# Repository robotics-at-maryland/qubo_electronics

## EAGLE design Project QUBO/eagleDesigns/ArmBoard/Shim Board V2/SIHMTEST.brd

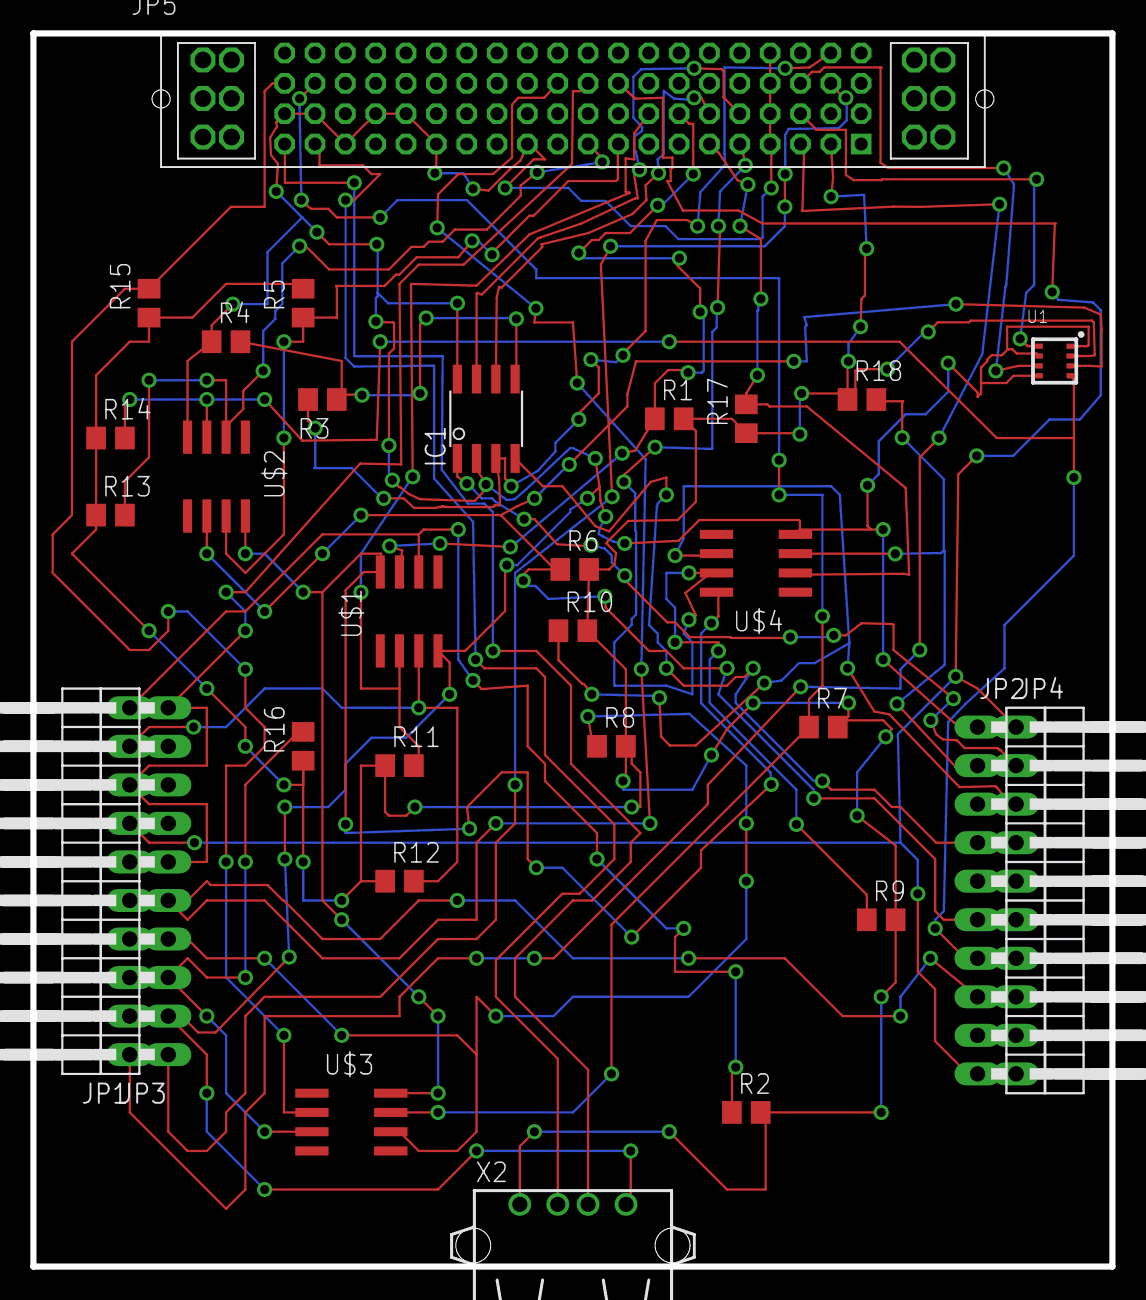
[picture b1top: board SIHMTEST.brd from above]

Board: 2 copper layers, 71.1 x 81.3 mm, 30 parts (0 on the bottom side), 34 nets.

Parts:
IC1: MCP2551/SN; SO08
JP1, JP2, JP3, JP4: 1X10/90
JP5: MPSC-01-80
R1, R2, R5, R6, R7, R8, R9, R10, R11, R12, R13, R14, R15, R16, R17, R18: 5k; R0805
R3, R4: 10k; R0805
U1: BME280; BME280_LGA
U$1, U$2, U$3, U$4: P82B715; SO8
X2: USB

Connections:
3.3(1): JP1.1, JP5.3
3.3(VDDBME): JP5.23, U1.P$8
3.3(VDDIOBME): JP5.43, U1.P$6
5.0(3): JP3.1, JP5.42
5.0(BME): JP5.2, R1.2, R2.2, R5.2, R6.2, R7.2, R8.2, R9.2, R10.2, R11.1, R12.1, R13.1, R14.1, R15.1, R16.1, R17.1, R18.1, U1.P$2, X2.1
BUFFERSCL0: JP5.28, R11.2, U$1.2
BUFFERSCL1: JP5.10, R13.2, U$2.2
BUFFERSCL2: JP5.60, R15.2, U$3.2
BUFFERSCL3: JP5.6, R17.2, U$4.2
BUFFERSDA0: JP5.27, R1.1, U$1.7
BUFFERSDA1: JP5.9, R5.1, U$2.7
BUFFERSDA2: JP5.59, R7.1, U$3.7
BUFFERSDA3: JP5.5, R9.1, U$4.7
BUFFERVCC: U$1.8, U$2.8, U$3.8, U$4.8
CANH: IC1.7, JP5.25
CANL: IC1.6, JP5.26
CANRX: IC1.4, JP2.4
CANTX: IC1.1, JP4.2
GND: IC1.2, IC1.8, JP2.1, JP3.2, JP5.4, JP5.12, JP5.15, JP5.18, JP5.24, JP5.36, JP5.37, JP5.39, JP5.40, JP5.44, JP5.64, R4.1, U1.P$1, U1.P$5, U1.P$7, U$1.4, U$2.4, U$4.4, X2.4
MISO: JP2.8, JP3.5, JP5.51
MOSI: JP1.8, JP3.6, JP3.10, JP5.50
unnamed: IC1.5, R3.1, R4.2
SPI_CLK: JP1.7, JP2.10, JP4.1, JP5.49
UNBUFFERSCL0: JP1.9, R12.2, U$1.3
UNBUFFERSCL1: JP2.7, R14.2, U1.P$4, U$2.3
UNBUFFERSCL2: JP3.3, R16.2, U$3.3
UNBUFFERSCL3: JP2.2, R18.2, U$4.3
UNBUFFERSDA0: JP1.10, R2.1, U$1.6
UNBUFFERSDA1: JP2.6, R6.1, U1.P$3, U$2.6
UNBUFFERSDA2: JP3.4, R8.1, U$3.6
UNBUFFERSDA3: JP4.3, R10.1, U$4.6
USB+: JP5.20, X2.3
USB-: JP5.19, X2.2
VDD: IC1.3, JP5.62, R3.2

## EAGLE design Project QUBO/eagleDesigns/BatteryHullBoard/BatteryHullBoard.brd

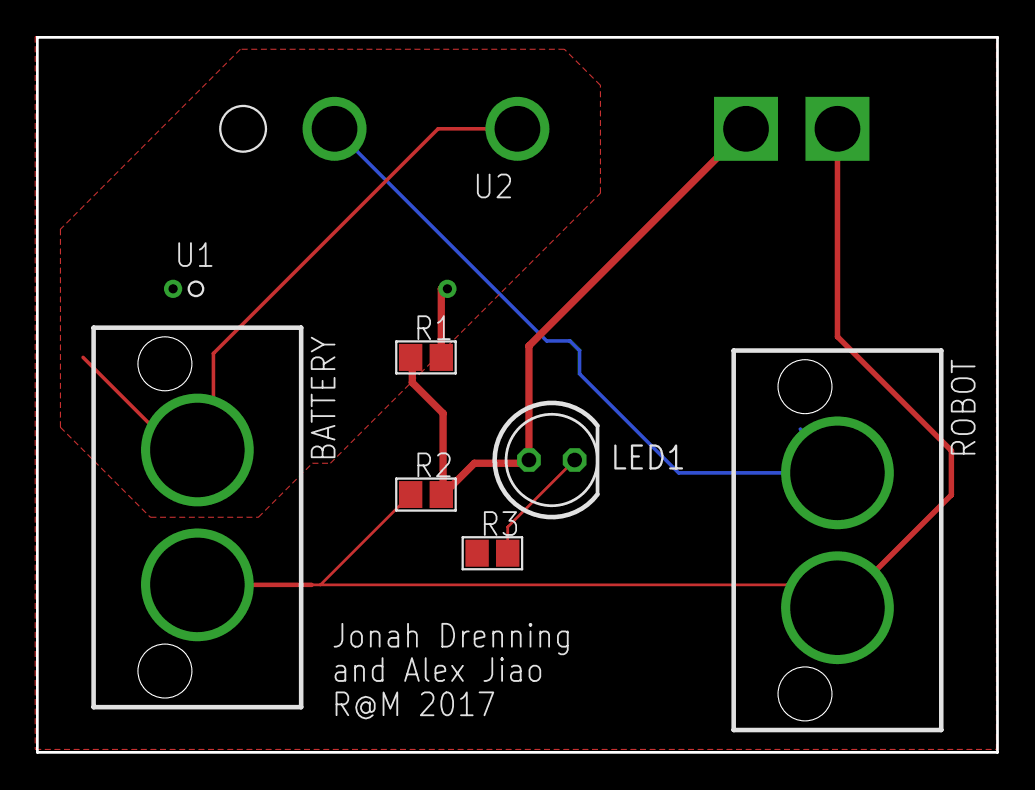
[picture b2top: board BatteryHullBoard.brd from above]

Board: 2 copper layers, 53.3 x 39.7 mm, 8 parts (0 on the bottom side), 6 nets.

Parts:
BATTERY: 2_SUPERSABRE; SUPERSABRE_2CIRCUIT
LED1: LED5MM
R1: 1000; R0805
R2: 7700; R0805
R3: 10000; R0805
ROBOT: 2_SUPERSABRE; SUPERSABRE_2CIRCUIT
U1: KSK-1E66
U2: CMXSIPSSR

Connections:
GND: BATTERY.P$2, R2.1, R3.1, ROBOT.P$2, U2.P$4
unnamed: R1.2, U1.P$2
unnamed: LED1.A, R1.1, R2.2, U2.P$3
unnamed: LED1.K, R3.2
PWR1: BATTERY.P$1, U1.P$1, U2.P$2
PWR2: ROBOT.P$1, U2.P$1

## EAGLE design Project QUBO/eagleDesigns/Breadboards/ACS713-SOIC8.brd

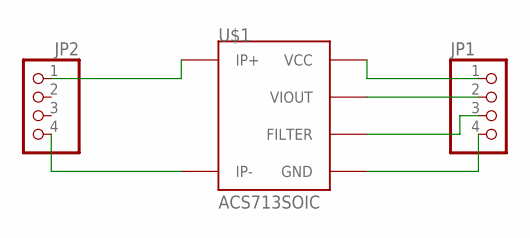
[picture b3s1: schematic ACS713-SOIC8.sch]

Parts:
JP1, JP2: PINHD-1X4; 1X04
U$1: ACS713SOIC; ACS713-SOIC

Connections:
unnamed: JP2.1, U$1.P$1 (IP+), U$1.P$2 (IP+)
unnamed: JP2.4, U$1.P$3 (IP-), U$1.P$4 (IP-)
unnamed: JP1.4, U$1.P$5 (GND)
unnamed: JP1.3, U$1.P$6 (FILTER)
unnamed: JP1.2, U$1.P$7 (VIOUT)
unnamed: JP1.1, U$1.P$8 (VCC)

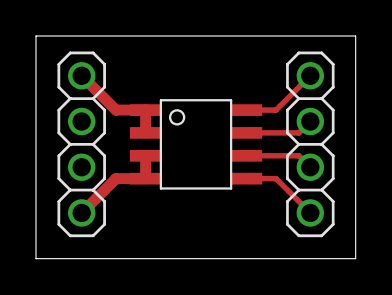
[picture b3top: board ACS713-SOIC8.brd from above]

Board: 2 copper layers, 17.8 x 12.4 mm, 3 parts (0 on the bottom side), 6 nets.

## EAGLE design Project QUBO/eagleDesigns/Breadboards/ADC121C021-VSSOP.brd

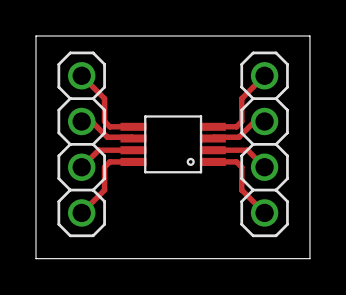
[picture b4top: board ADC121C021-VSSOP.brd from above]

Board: 2 copper layers, 15.2 x 12.4 mm, 3 parts (0 on the bottom side), 8 nets.

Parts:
JP1, JP2: 1X04
U$1: ADC121C021; VSSOP-8

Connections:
unnamed: JP1.1, U$1.P$1
unnamed: JP1.2, U$1.P$2
unnamed: JP1.3, U$1.P$3
unnamed: JP1.4, U$1.P$4
unnamed: JP2.1, U$1.P$5
unnamed: JP2.2, U$1.P$6
unnamed: JP2.3, U$1.P$7
unnamed: JP2.4, U$1.P$8

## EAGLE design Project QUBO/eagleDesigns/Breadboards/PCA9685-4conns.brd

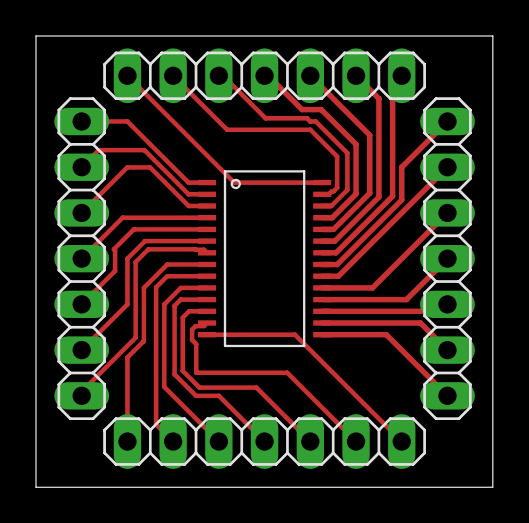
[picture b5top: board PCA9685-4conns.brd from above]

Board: 2 copper layers, 25.4 x 25.1 mm, 5 parts (0 on the bottom side), 28 nets.

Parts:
JP1, JP2, JP3, JP4: 1X07
U1: PCA9685; TSSOP-28_4MM

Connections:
unnamed: JP3.1, U1.1
unnamed: JP3.2, U1.2
unnamed: JP3.3, U1.3
unnamed: JP3.4, U1.4
unnamed: JP3.5, U1.5
unnamed: JP3.6, U1.6
unnamed: JP3.7, U1.7
unnamed: JP4.1, U1.8
unnamed: JP4.3, U1.10
unnamed: JP4.2, U1.9
unnamed: JP4.4, U1.11
unnamed: JP4.5, U1.12
unnamed: JP4.6, U1.13
unnamed: JP4.7, U1.14
unnamed: JP2.7, U1.15
unnamed: JP2.6, U1.16
unnamed: JP2.5, U1.17
unnamed: JP2.4, U1.18
unnamed: JP2.3, U1.19
unnamed: JP2.2, U1.20
unnamed: JP2.1, U1.21
unnamed: JP1.7, U1.22
unnamed: JP1.6, U1.23
unnamed: JP1.5, U1.24
unnamed: JP1.4, U1.25
unnamed: JP1.3, U1.26
unnamed: JP1.2, U1.27
unnamed: JP1.1, U1.28
